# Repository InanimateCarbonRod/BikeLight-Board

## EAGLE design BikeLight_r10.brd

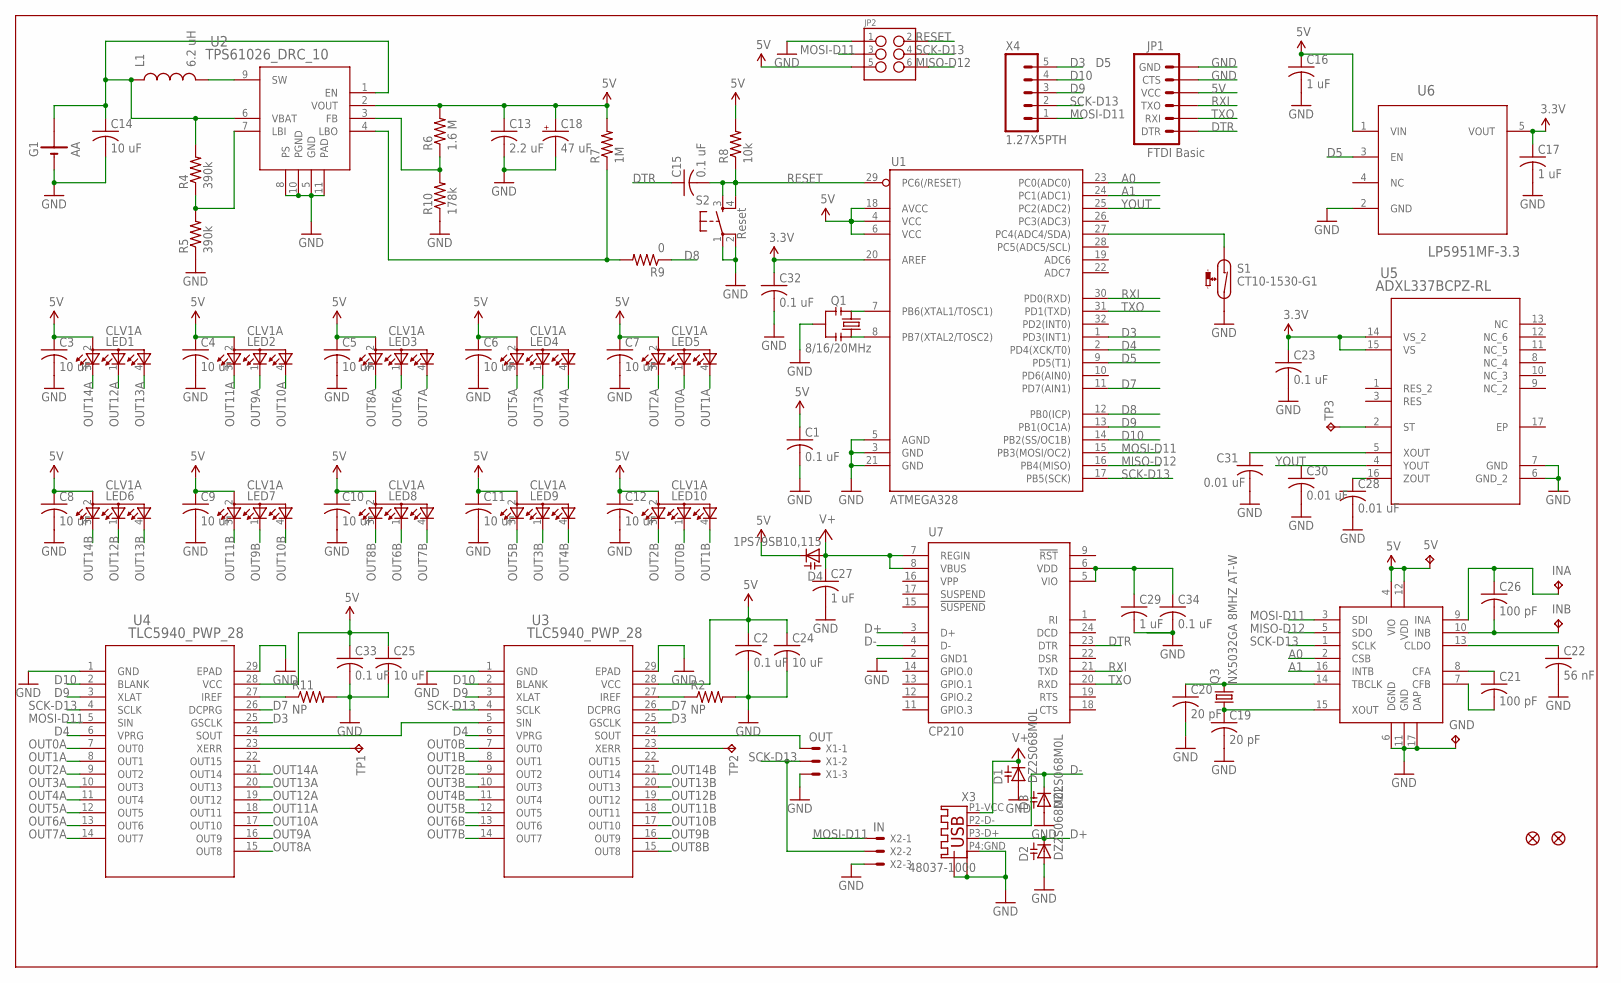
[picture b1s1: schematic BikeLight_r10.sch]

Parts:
5V: TPPAD1-13; P1-13
C1, C2, C15, C23, C32, C33, C34: 0.1 uF; C0402
C3, C4, C5, C6, C7, C8, C9, C10, C11, C12: 10 uF; C0805
C13: 2.2 uF; C0805K
C14, C24, C25: 10 uF; C0805K
C16, C17, C27, C29: 1 uF; C0402
C18: 47 uF; CT6032
C19, C20: 20 pF; C0402
C21, C26: 100 pF; C0805K
C22: 56 nF; C0402
C28, C30, C31: 0.01 uF; C0402
D1, D2, D3: DZ2S068M0L; SOD523
D4: 1PS79SB10,115; SOD523
G1: AA; AA_BATTERY
GND: TPPAD1-13; P1-13
INA: TPPAD1-13; P1-13
INB: TPPAD1-13; P1-13
JP1: FTDI Basic; 1X06
JP2: M03X2POGO_PINS; 2X3_POGO
L1: 6.2 uH; CDRH52D
LED1, LED2, LED3, LED4, LED5, LED6, LED7, LED8, LED9, LED10: CLV1A; P-LCC-4-3
Q1: 8/16/20MHz; RESONATOR-SMD
Q3: NX5032GA 8MHZ AT-W; FC-12M
R2, R11: NP; R0402
R4, R5: 390k; R0402
R6: 1.6 M; R0805
R7: 1M; R0805
R8: 10k; R0402
R9: 0; R0805
R10: 178k; R0805
S1: CT10-1530-G1; CT10-G1
S2: Reset; TACTILE_SWITCH_SMD
TP1, TP2, TP3: TPB1,27; B1,27
U1: ATMEGA328; TQFP32-08
U2: TPS61026_DRC_10; DRC10_2P4X1P65
U3, U4: TLC5940_PWP_28; PWP28_6P17X2P4
U5: ADXL337BCPZ-RL; CP_16_28
U6: LP5951MF-3.3; SOT95P285X120-5N
U7: CP210; QFN24-4X4
U8: LDC1000; WSON-16
U$2, U$4: FIDUCIAL1X2; FIDUCIAL-1X2
X1: OUT; 22-23-2031
X2: IN; 22-23-2031
X3: 48037-1000; USB-A_PLUG
X4: 1.27X5PTH; 1X04-1.27MM

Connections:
3.3V: C17.1, C23.1, C32.1, U1.20 (AREF), U5.14 (VS_2), U5.15 (VS), U6.5 (VOUT)
5V: 5V.TP, C1.1, C2.1, C3.1, C4.1, C5.1, C6.1, C7.1, C8.1, C9.1, C10.1, C11.1, C12.1, C13.1, C16.1, C18.+, C24.1, C25.1, C33.1, D4.C, JP1.4 (VCC), JP2.P$5 (5), LED1.2 (A2), LED2.2 (A2), LED3.2 (A2), LED4.2 (A2), LED5.2 (A2), LED6.2 (A2), LED7.2 (A2), LED8.2 (A2), LED9.2 (A2), LED10.2 (A2), R6.2, R7.2, R8.2, U1.4 (VCC), U1.6 (VCC), U1.18 (AVCC), U2.2 (VOUT), U3.28 (VCC), U4.28 (VCC), U6.1 (VIN), U8.4 (VIO), U8.12 (VDD)
A0: U1.23 (PC0(ADC0)), U8.2 (CSB)
A1: U1.24 (PC1(ADC1)), U8.16 (INTB)
D3: U1.1 (PD3(INT1)), U3.25 (GSCLK), U4.25 (GSCLK), X4.5
D4: U1.2 (PD4(XCK/T0)), U3.6 (VPRG), U4.6 (VPRG)
D5: U1.9 (PD5(T1)), U6.3 (EN)
D7: U1.11 (PD7(AIN1)), U3.26 (DCPRG), U4.26 (DCPRG)
D8: R9.1, U1.12 (PB0(ICP))
D9: U1.13 (PB1(OC1A)), U3.3 (XLAT), U4.3 (XLAT), X4.3
D10: U1.14 (PB2(SS/OC1B)), U3.2 (BLANK), U4.2 (BLANK), X4.4
D+: D2.C, U7.3 (D+), X3.P3-D+ (3)
D-: D3.C, U7.4 (D-), X3.P2-D- (2)
DTR: C15.1, JP1.1 (DTR), U7.23 (DTR)
GND: C1.2, C2.2, C3.2, C4.2, C5.2, C6.2, C7.2, C8.2, C9.2, C10.2, C11.2, C12.2, C13.2, C14.2, C16.2, C17.2, C18.-, C19.2, C20.2, C22.2, C23.2, C24.2, C25.2, C27.2, C28.2, C29.2, C30.2, C31.2, C32.2, C33.2, C34.2, D1.A, D2.A, D3.A, G1.P$2- (-), GND.TP, JP1.5 (CTS), JP1.6 (GND), JP2.P$1 (1), Q1.2, R2.2, R5.1, R10.1, R11.2, S1.2, S2.1, S2.2, U1.3 (GND), U1.5 (AGND), U1.21 (GND), U2.5 (GND), U2.8 (PS), U2.10 (PGND), U2.11 (PAD), U3.1 (GND), U3.29 (EPAD), U4.1 (GND), U4.29 (EPAD), U5.6 (GND_2), U5.7 (GND), U6.2 (GND), U7.2 (GND1), U8.6 (DGND), U8.11 (GND), U8.17 (DAP), X1.3, X2.3, X3.P4:GND (4), X3.P$5 (SHLD1), X3.P$6 (SHLD2)
MISO-D12: JP2.P$6 (6), U1.16 (PB4(MISO)), U8.5 (SDO)
MOSI-D11: JP2.P$3 (3), U1.15 (PB3(MOSI/OC2)), U4.5 (SIN), U8.3 (SDI), X2.1, X4.1
unnamed: Q1.1, U1.8 (PB7(XTAL2/TOSC2))
unnamed: Q1.3, U1.7 (PB6(XTAL1/TOSC1))
unnamed: U3.5 (SIN), U4.24 (SOUT)
unnamed: U3.24 (SOUT), X1.1
unnamed: TP1.TP, U4.23 (XERR)
unnamed: TP2.TP, U3.23 (XERR)
unnamed: R4.1, R5.2, U2.7 (LBI)
unnamed: R6.1, R10.2, U2.3 (FB)
unnamed: R2.1, U3.27 (IREF)
unnamed: C14.1, G1.P$1+ (+), L1.1, R4.2, U2.1 (EN), U2.6 (VBAT)
unnamed: L1.2, U2.9 (SW)
unnamed: R7.1, R9.2, U2.4 (LBO)
unnamed: TP3.TP, U5.2 (ST)
unnamed: C20.1, Q3.2, U8.14 (TBCLK)
unnamed: C19.1, Q3.1, U8.15 (XOUT)
unnamed: R11.1, U4.27 (IREF)
unnamed: C21.1, U8.8 (CFA)
unnamed: C21.2, U8.7 (CFB)
unnamed: C26.2, INB.TP, U8.10 (INB)
unnamed: C22.1, U8.13 (CLDO)
unnamed: C29.1, C34.1, U7.5 (VIO), U7.6 (VDD)
unnamed: C26.1, INA.TP, U8.9 (INA)
unnamed: C31.1, U5.5 (XOUT)
unnamed: S1.1, U1.27 (PC4(ADC4/SDA))
OUT0A: LED5.1 (CBLUE), U4.7 (OUT0)
OUT0B: LED10.1 (CBLUE), U3.7 (OUT0)
OUT1A: LED5.4 (CGREEN), U4.8 (OUT1)
OUT1B: LED10.4 (CGREEN), U3.8 (OUT1)
OUT2A: LED5.3 (CRED), U4.9 (OUT2)
OUT2B: LED10.3 (CRED), U3.9 (OUT2)
OUT3A: LED4.1 (CBLUE), U4.10 (OUT3)
OUT3B: LED9.1 (CBLUE), U3.10 (OUT3)
OUT4A: LED4.4 (CGREEN), U4.11 (OUT4)
OUT4B: LED9.4 (CGREEN), U3.11 (OUT4)
OUT5A: LED4.3 (CRED), U4.12 (OUT5)
OUT5B: LED9.3 (CRED), U3.12 (OUT5)
OUT6A: LED3.1 (CBLUE), U4.13 (OUT6)
OUT6B: LED8.1 (CBLUE), U3.13 (OUT6)
OUT7A: LED3.4 (CGREEN), U4.14 (OUT7)
OUT7B: LED8.4 (CGREEN), U3.14 (OUT7)
OUT8A: LED3.3 (CRED), U4.15 (OUT8)
OUT8B: LED8.3 (CRED), U3.15 (OUT8)
OUT9A: LED2.1 (CBLUE), U4.16 (OUT9)
OUT9B: LED7.1 (CBLUE), U3.16 (OUT9)
OUT10A: LED2.4 (CGREEN), U4.17 (OUT10)
OUT10B: LED7.4 (CGREEN), U3.17 (OUT10)
OUT11A: LED2.3 (CRED), U4.18 (OUT11)
OUT11B: LED7.3 (CRED), U3.18 (OUT11)
OUT12A: LED1.1 (CBLUE), U4.19 (OUT12)
OUT12B: LED6.1 (CBLUE), U3.19 (OUT12)
OUT13A: LED1.4 (CGREEN), U4.20 (OUT13)
OUT13B: LED6.4 (CGREEN), U3.20 (OUT13)
OUT14A: LED1.3 (CRED), U4.21 (OUT14)
OUT14B: LED6.3 (CRED), U3.21 (OUT14)
RESET: C15.2, JP2.P$2 (2), R8.1, S2.3, S2.4, U1.29 (PC6(/RESET))
RXI: JP1.3 (TXO), U1.30 (PD0(RXD)), U7.21 (TXD)
SCK-D13: JP2.P$4 (4), U1.17 (PB5(SCK)), U3.4 (SCLK), U4.4 (SCLK), U8.1 (SCLK), X1.2, X2.2, X4.2
TXO: JP1.2 (RXI), U1.31 (PD1(TXD)), U7.20 (RXD)
V+: C27.1, D1.C, D4.A, U7.7 (REGIN), U7.8 (VBUS), X3.P1-VCC (1)
YOUT: C30.1, U1.25 (PC2(ADC2)), U5.4 (YOUT)
ZOUT: C28.1, U5.16 (ZOUT)

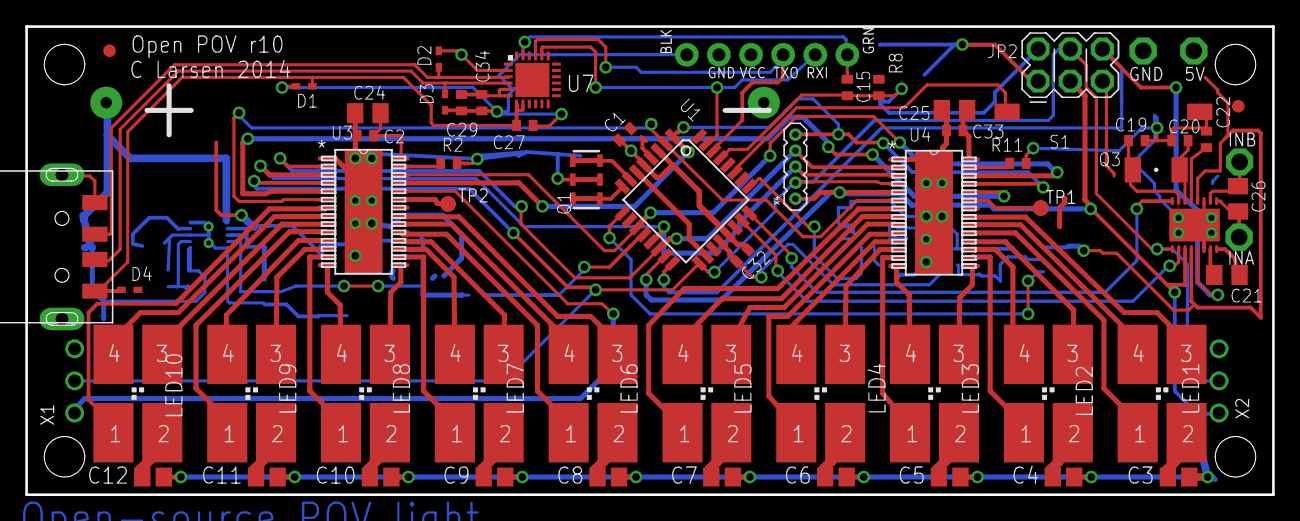
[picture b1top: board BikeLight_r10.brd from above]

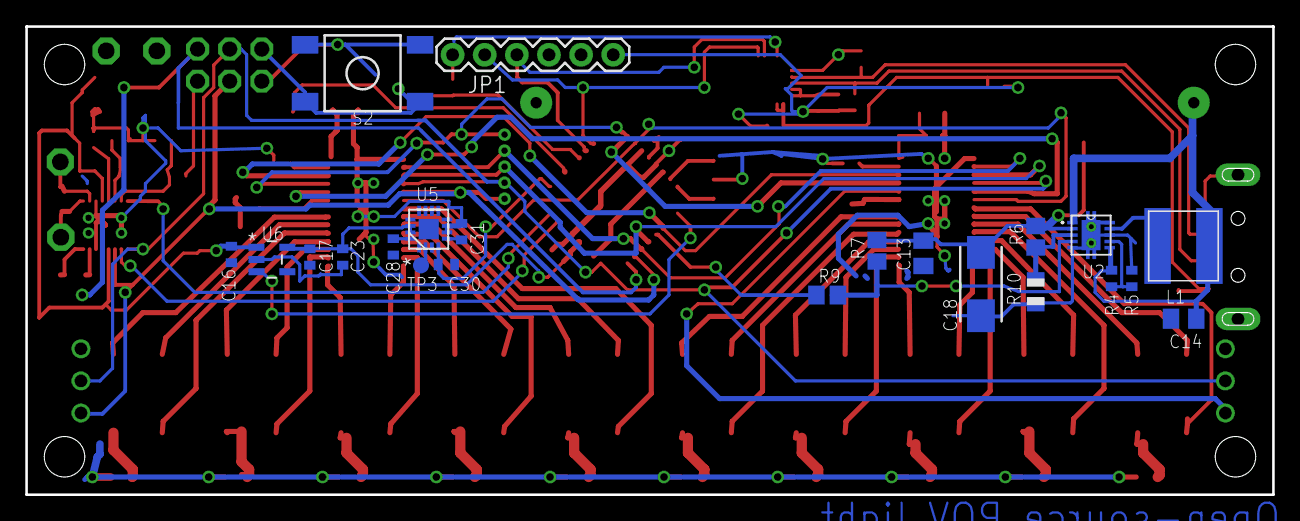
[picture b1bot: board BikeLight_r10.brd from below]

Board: 2 copper layers, 98.6 x 37.0 mm, 86 parts (22 on the bottom side), 78 nets.

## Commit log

2015-07-08 removing board backup files
2015-07-08 Removing unnecessary .zip

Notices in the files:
BikeLight_r10.brd:
Released under the Creative Commons Attribution Share-Alike 3.0 License
http://creativecommons.org/licenses/by-sa/3.0
parts and their libraries:
Inductor-SumidaCDRH5D28: Licensing: CC v3.0 Share-Alike You are welcome to use this library for commercial purposes.
